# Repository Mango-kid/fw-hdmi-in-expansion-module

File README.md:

# Description
An HDMI input expansion module for the FW laptop. It utalizes the MS213x. As far as I can tell this is the highest preformance HDMI capture chip avalible that can fit in this package and not require serious thermal considerations. 
- USB3.0
- 100ms or better latency at 1080 in MJPEG mode (glass to glass, capture only will be less)

## Status
- hardware being prototyped and tested

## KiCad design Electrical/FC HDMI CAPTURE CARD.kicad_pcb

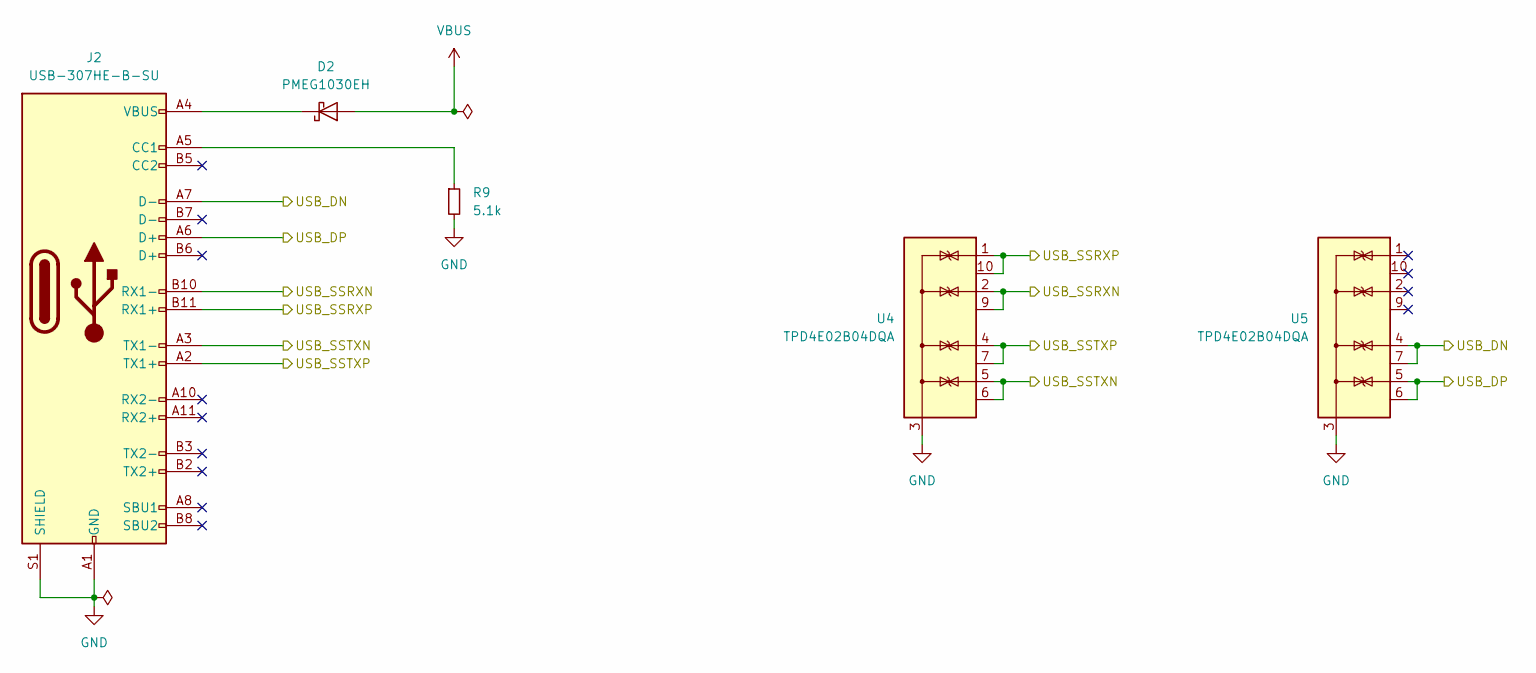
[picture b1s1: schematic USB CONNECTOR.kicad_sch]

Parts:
D2: PMEG1030EH; D_SOD-123F
J2: USB-307HE-B-SU; USB-TYPE-C-SMD_USB-307HE-B-SU
R9: 5.1k; R_0402_1005Metric
U4, U5: TPD4E02B04DQA; USON-10_2.5x1.0mm_P0.5mm

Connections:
/CAPTURE CONTROLLER/USB_DN: J2.A7 (D-), U5.4 (IO3), U5.7 (NC); also elsewhere on the board
/CAPTURE CONTROLLER/USB_DP: J2.A6 (D+), U5.5 (IO4), U5.6 (NC); also elsewhere on the board
/CAPTURE CONTROLLER/USB_SSRXN: J2.B10 (RX1-), U4.2 (IO2), U4.9 (NC); also elsewhere on the board
/CAPTURE CONTROLLER/USB_SSRXP: J2.B11 (RX1+), U4.1 (IO1), U4.10 (NC); also elsewhere on the board
/CAPTURE CONTROLLER/USB_SSTXN: J2.A3 (TX1-), U4.5 (IO4), U4.6 (NC); also elsewhere on the board
/CAPTURE CONTROLLER/USB_SSTXP: J2.A2 (TX1+), U4.4 (IO3), U4.7 (NC); also elsewhere on the board
GND: J2.A1 (GND), J2.A12 (GND), J2.B1 (GND), J2.B12 (GND), J2.S1 (SHIELD), R9.2, U4.3 (G), U4.8 (G), U5.3 (G), U5.8 (G); also elsewhere on the board
unnamed: D2.1 (K), J2.A4 (VBUS), J2.A9 (VBUS), J2.B4 (VBUS), J2.B9 (VBUS)
unnamed: J2.A5 (CC1), R9.1
VBUS: D2.2 (A); also elsewhere on the board

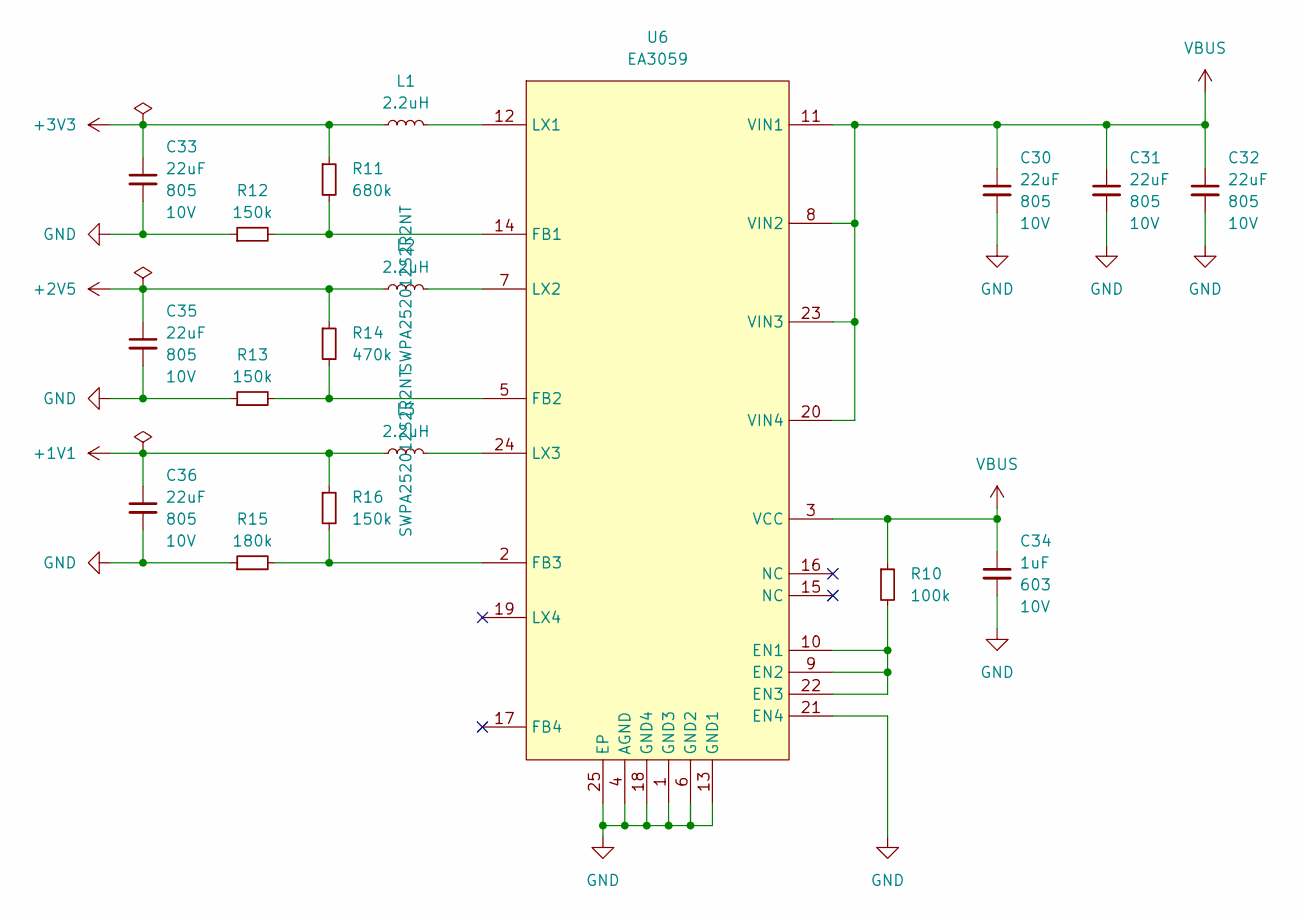
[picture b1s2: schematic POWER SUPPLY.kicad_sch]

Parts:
C30, C31, C32, C33, C35, C36: 22uF; C_0805_2012Metric; VOLTAGE 10V
C34: 1uF; C_0603_1608Metric; VOLTAGE 10V
L1, L2, L3: 2.2uH; L_1008_2520Metric; MPN SWPA252012S2R2NT
R10: 100k; R_0402_1005Metric
R11: 680k; R_0402_1005Metric
R12, R13, R16: 150k; R_0402_1005Metric
R14: 470k; R_0402_1005Metric
R15: 180k; R_0402_1005Metric
U6: EA3059; QFN-24-1EP_4x4mm_P0.5mm_EP2.5x2.5mm

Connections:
+1V1: C36.1, L3.1, R16.1; also elsewhere on the board
+2V5: C35.1, L2.1, R14.1; also elsewhere on the board
+3V3: C33.1, L1.1, R11.1; also elsewhere on the board
GND: C30.2, C31.2, C32.2, C33.2, C34.2, C35.2, C36.2, R12.1, R13.1, R15.1, U6.1 (GND3), U6.4 (AGND), U6.6 (GND2), U6.13 (GND1), U6.18 (GND4), U6.21 (EN4), U6.25 (EP); also elsewhere on the board
unnamed: R10.2, U6.9 (EN2), U6.10 (EN1), U6.22 (EN3)
unnamed: R11.2, R12.2, U6.14 (FB1)
unnamed: R13.2, R14.2, U6.5 (FB2)
unnamed: R15.2, R16.2, U6.2 (FB3)
unnamed: L1.2, U6.12 (LX1)
unnamed: L2.2, U6.7 (LX2)
unnamed: L3.2, U6.24 (LX3)
VBUS: C30.1, C31.1, C32.1, C34.1, R10.1, U6.3 (VCC), U6.8 (VIN2), U6.11 (VIN1), U6.20 (VIN4), U6.23 (VIN3); also elsewhere on the board

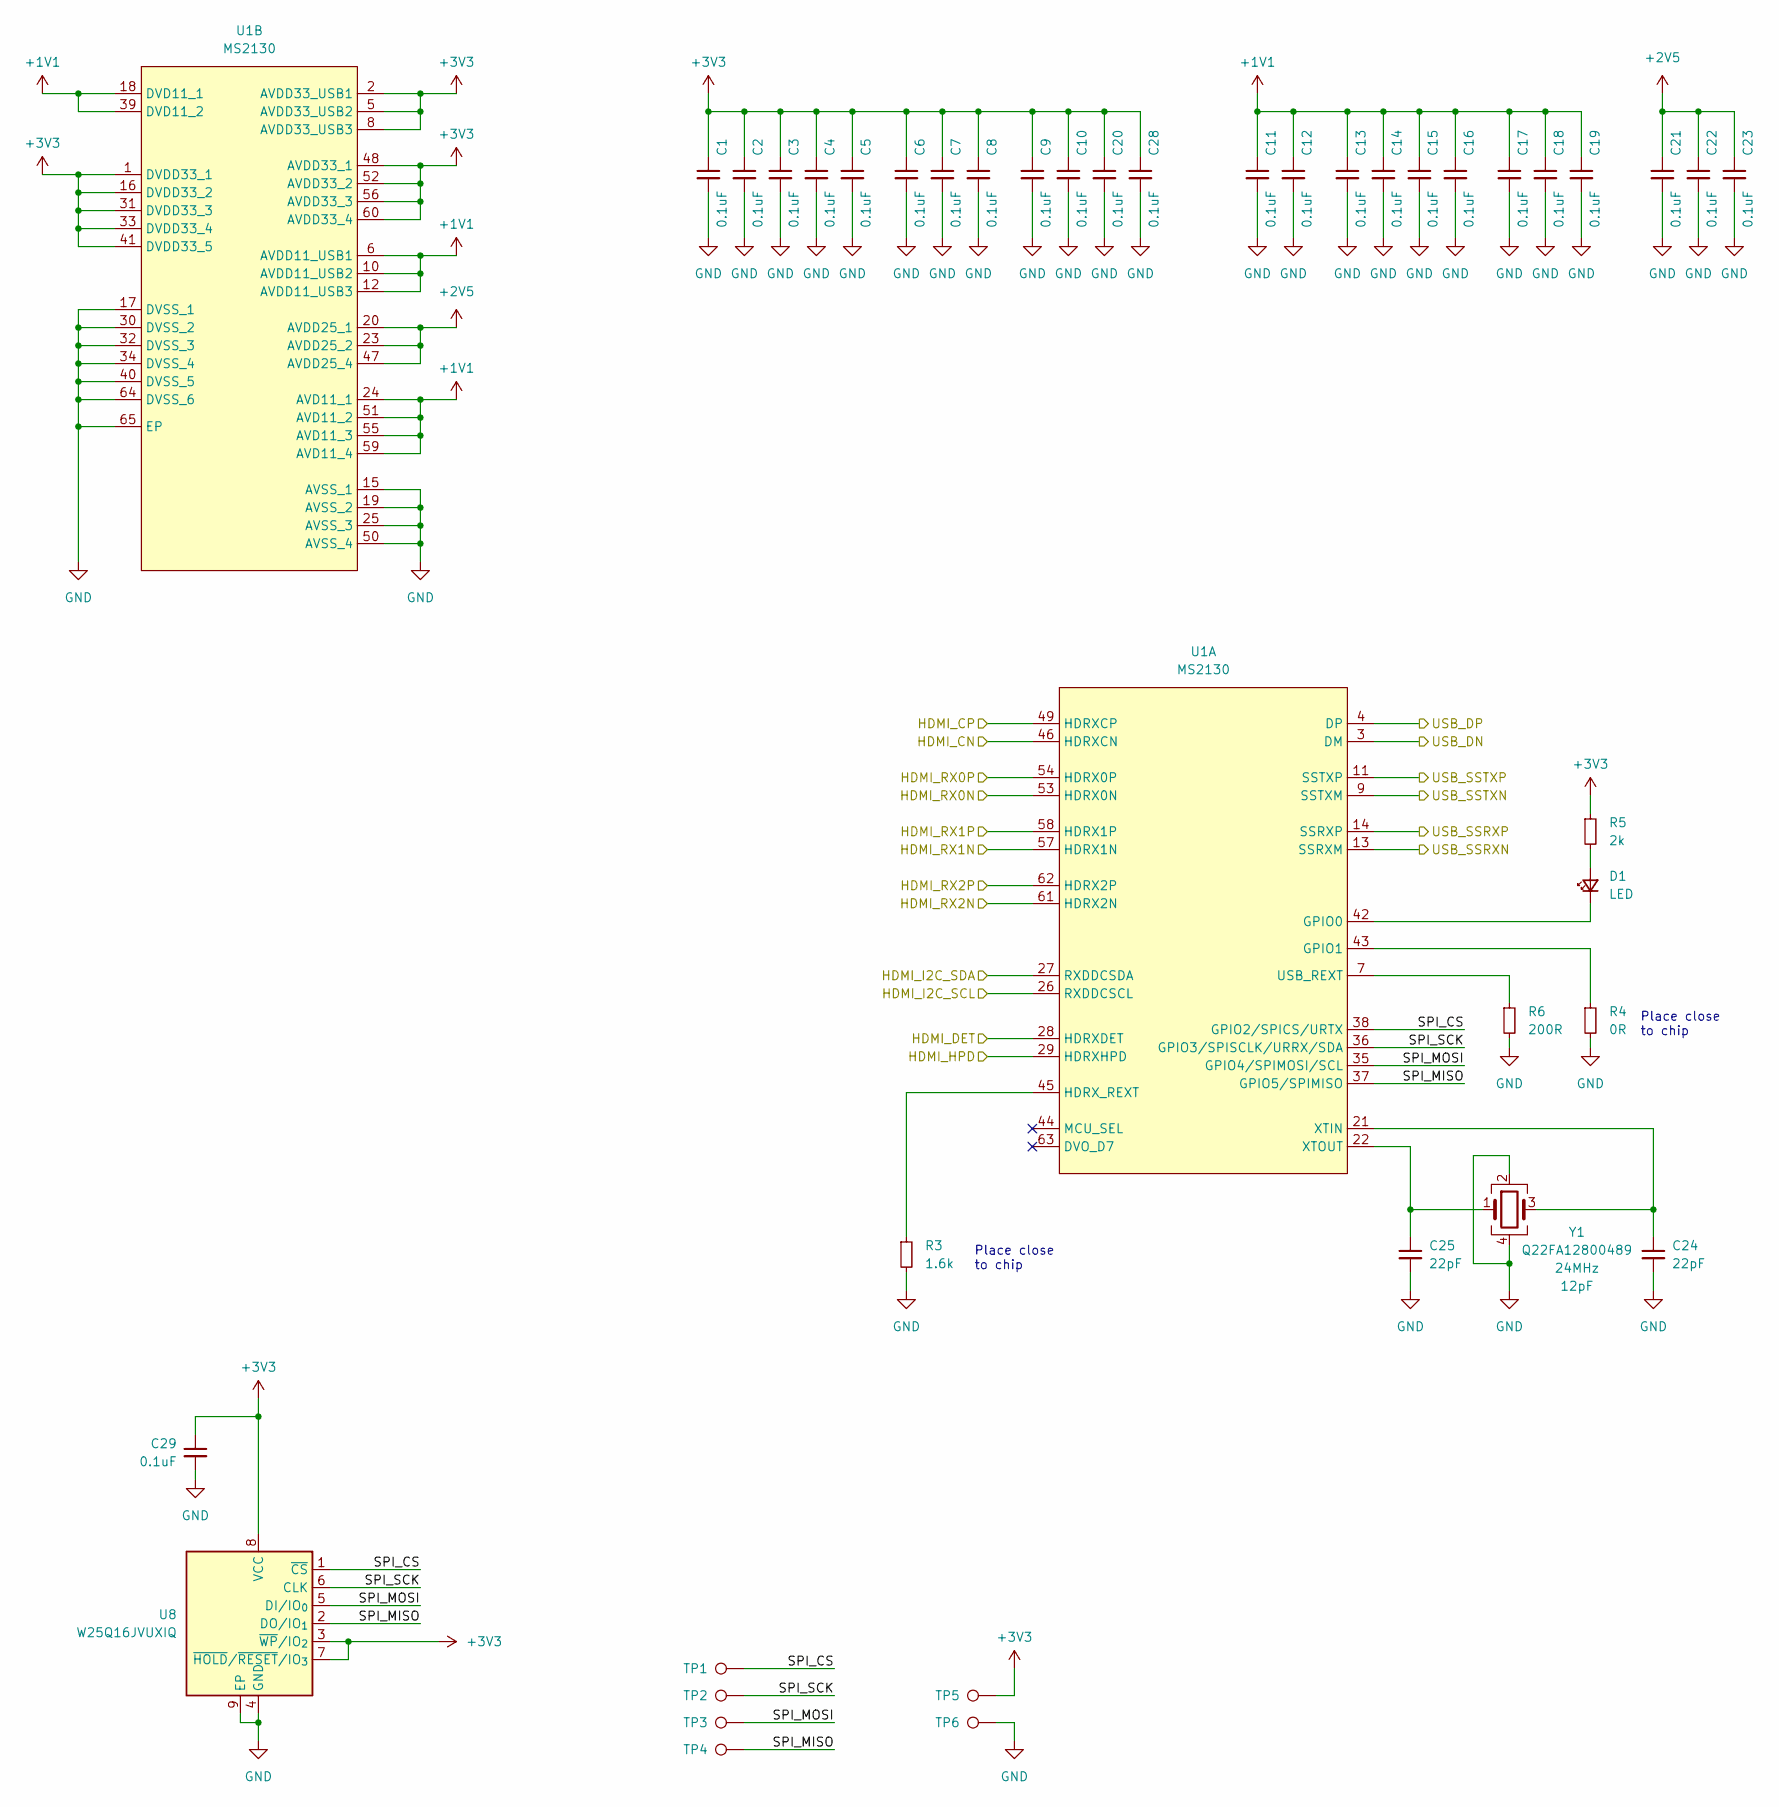
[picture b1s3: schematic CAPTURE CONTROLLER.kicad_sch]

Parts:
C1, C2, C3, C4, C5, C6, C7, C8, C9, C10, C11, C12, C13, C14, C15, C16, C17, C18, C19, C20, C21, C22, C23, C28, C29: 0.1uF; C_0402_1005Metric
C24, C25: 22pF; C_0402_1005Metric
D1: LED; LED_0402_1005Metric
R3: 1.6k; R_0402_1005Metric
R4: 0R; R_0402_1005Metric
R5: 2k; R_0402_1005Metric
R6: 200R; R_0402_1005Metric
TP1, TP2, TP3, TP4, TP5, TP6: TestPoint; TestPoint_Pad
U1: MS2130; QFN-64-1EP_9x9mm_P0.5mm_EP5.7x5.7mm
U8: W25Q16JVUXIQ; USON-8_L3.0-W2.0-P0.50-BL-EP
Y1: Q22FA12800489; Crystal_SMD_2016-4Pin_2.0x1.6mm

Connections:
+1V1: C11.1, C12.1, C13.1, C14.1, C15.1, C16.1, C17.1, C18.1, C19.1, U1.6 (AVDD11_USB1), U1.10 (AVDD11_USB2), U1.12 (AVDD11_USB3), U1.18 (DVD11_1), U1.24 (AVD11_1), U1.39 (DVD11_2), U1.51 (AVD11_2), U1.55 (AVD11_3), U1.59 (AVD11_4); also elsewhere on the board
+2V5: C21.1, C22.1, C23.1, U1.20 (AVDD25_1), U1.23 (AVDD25_2), U1.47 (AVDD25_4); also elsewhere on the board
+3V3: C1.1, C2.1, C3.1, C4.1, C5.1, C6.1, C7.1, C8.1, C9.1, C10.1, C20.1, C28.1, C29.1, R5.1, TP5.1, U1.1 (DVDD33_1), U1.2 (AVDD33_USB1), U1.5 (AVDD33_USB2), U1.8 (AVDD33_USB3), U1.16 (DVDD33_2), U1.31 (DVDD33_3), U1.33 (DVDD33_4), U1.41 (DVDD33_5), U1.48 (AVDD33_1), U1.52 (AVDD33_2), U1.56 (AVDD33_3), U1.60 (AVDD33_4), U8.3 (~WP/IO_{2}), U8.7 (~HOLD/~RESET/IO_{3}), U8.8 (VCC); also elsewhere on the board
/CAPTURE CONTROLLER/HDMI_CN: U1.46 (HDRXCN); also elsewhere on the board
/CAPTURE CONTROLLER/HDMI_CP: U1.49 (HDRXCP); also elsewhere on the board
/CAPTURE CONTROLLER/HDMI_DET: U1.28 (HDRXDET); also elsewhere on the board
/CAPTURE CONTROLLER/HDMI_HPD: U1.29 (HDRXHPD); also elsewhere on the board
/CAPTURE CONTROLLER/HDMI_I2C_SCL: U1.26 (RXDDCSCL); also elsewhere on the board
/CAPTURE CONTROLLER/HDMI_I2C_SDA: U1.27 (RXDDCSDA); also elsewhere on the board
/CAPTURE CONTROLLER/HDMI_RX0N: U1.53 (HDRX0N); also elsewhere on the board
/CAPTURE CONTROLLER/HDMI_RX0P: U1.54 (HDRX0P); also elsewhere on the board
/CAPTURE CONTROLLER/HDMI_RX1N: U1.57 (HDRX1N); also elsewhere on the board
/CAPTURE CONTROLLER/HDMI_RX1P: U1.58 (HDRX1P); also elsewhere on the board
/CAPTURE CONTROLLER/HDMI_RX2N: U1.61 (HDRX2N); also elsewhere on the board
/CAPTURE CONTROLLER/HDMI_RX2P: U1.62 (HDRX2P); also elsewhere on the board
/CAPTURE CONTROLLER/SPI_CS: TP1.1, U1.38 (GPIO2/SPICS/URTX), U8.1 (~CS)
/CAPTURE CONTROLLER/SPI_MISO: TP4.1, U1.37 (GPIO5/SPIMISO), U8.2 (DO/IO_{1})
/CAPTURE CONTROLLER/SPI_MOSI: TP3.1, U1.35 (GPIO4/SPIMOSI/SCL), U8.5 (DI/IO_{0})
/CAPTURE CONTROLLER/SPI_SCK: TP2.1, U1.36 (GPIO3/SPISCLK/URRX/SDA), U8.6 (CLK)
/CAPTURE CONTROLLER/USB_DN: U1.3 (DM); also elsewhere on the board
/CAPTURE CONTROLLER/USB_DP: U1.4 (DP); also elsewhere on the board
/CAPTURE CONTROLLER/USB_SSRXN: U1.13 (SSRXM); also elsewhere on the board
/CAPTURE CONTROLLER/USB_SSRXP: U1.14 (SSRXP); also elsewhere on the board
/CAPTURE CONTROLLER/USB_SSTXN: U1.9 (SSTXM); also elsewhere on the board
/CAPTURE CONTROLLER/USB_SSTXP: U1.11 (SSTXP); also elsewhere on the board
GND: C1.2, C2.2, C3.2, C4.2, C5.2, C6.2, C7.2, C8.2, C9.2, C10.2, C11.2, C12.2, C13.2, C14.2, C15.2, C16.2, C17.2, C18.2, C19.2, C20.2, C21.2, C22.2, C23.2, C24.2, C25.2, C28.2, C29.2, R3.2, R4.2, R6.2, TP6.1, U1.15 (AVSS_1), U1.17 (DVSS_1), U1.19 (AVSS_2), U1.25 (AVSS_3), U1.30 (DVSS_2), U1.32 (DVSS_3), U1.34 (DVSS_4), U1.40 (DVSS_5), U1.50 (AVSS_4), U1.64 (DVSS_6), U1.65 (EP), U8.4 (GND), U8.9 (EP), Y1.2, Y1.4; also elsewhere on the board
unnamed: D1.2 (A), R5.2
unnamed: D1.1 (K), U1.42 (GPIO0)
unnamed: R4.1, U1.43 (GPIO1)
unnamed: R3.1, U1.45 (HDRX_REXT)
unnamed: R6.1, U1.7 (USB_REXT)
unnamed: C24.1, U1.21 (XTIN), Y1.3
unnamed: C25.1, U1.22 (XTOUT), Y1.1

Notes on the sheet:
Place close to chip

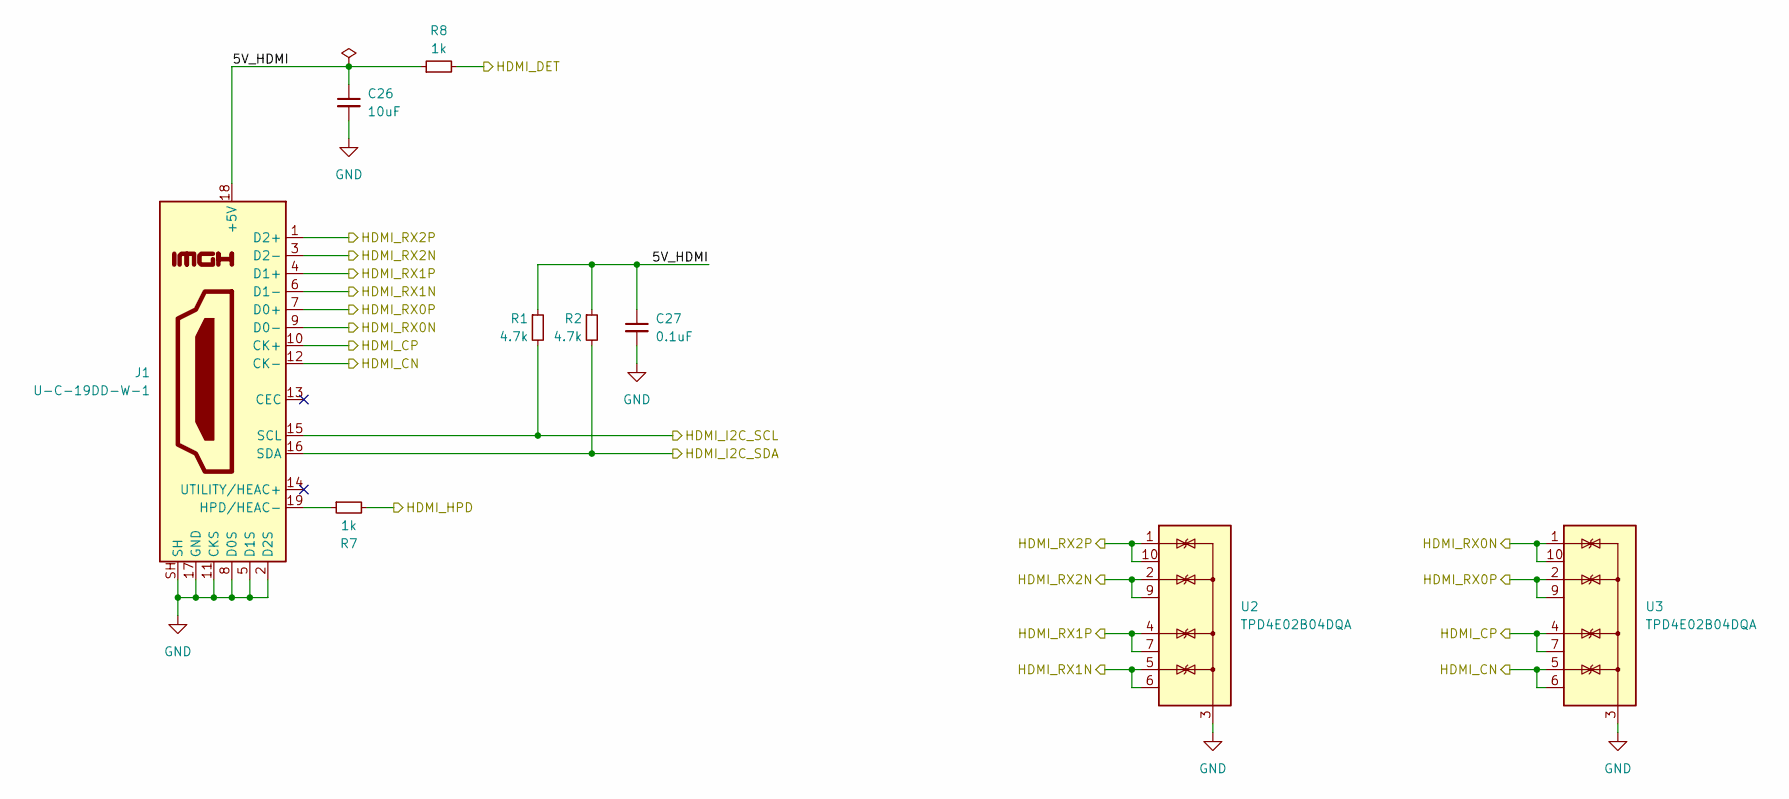
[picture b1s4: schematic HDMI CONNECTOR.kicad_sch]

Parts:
C26: 10uF; C_0603_1608Metric
C27: 0.1uF; C_0402_1005Metric
J1: U-C-19DD-W-1; SAMESKY_HD06-19-RVS-MSMT-TR
R1, R2: 4.7k; R_0402_1005Metric
R7, R8: 1k; R_0402_1005Metric
U2, U3: TPD4E02B04DQA; USON-10_2.5x1.0mm_P0.5mm

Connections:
/CAPTURE CONTROLLER/HDMI_CN: J1.12 (CK-), U3.5 (IO4), U3.6 (NC); also elsewhere on the board
/CAPTURE CONTROLLER/HDMI_CP: J1.10 (CK+), U3.4 (IO3), U3.7 (NC); also elsewhere on the board
/CAPTURE CONTROLLER/HDMI_DET: R8.2; also elsewhere on the board
/CAPTURE CONTROLLER/HDMI_HPD: R7.2; also elsewhere on the board
/CAPTURE CONTROLLER/HDMI_I2C_SCL: J1.15 (SCL), R1.2; also elsewhere on the board
/CAPTURE CONTROLLER/HDMI_I2C_SDA: J1.16 (SDA), R2.2; also elsewhere on the board
/CAPTURE CONTROLLER/HDMI_RX0N: J1.9 (D0-), U3.1 (IO1), U3.10 (NC); also elsewhere on the board
/CAPTURE CONTROLLER/HDMI_RX0P: J1.7 (D0+), U3.2 (IO2), U3.9 (NC); also elsewhere on the board
/CAPTURE CONTROLLER/HDMI_RX1N: J1.6 (D1-), U2.5 (IO4), U2.6 (NC); also elsewhere on the board
/CAPTURE CONTROLLER/HDMI_RX1P: J1.4 (D1+), U2.4 (IO3), U2.7 (NC); also elsewhere on the board
/CAPTURE CONTROLLER/HDMI_RX2N: J1.3 (D2-), U2.2 (IO2), U2.9 (NC); also elsewhere on the board
/CAPTURE CONTROLLER/HDMI_RX2P: J1.1 (D2+), U2.1 (IO1), U2.10 (NC); also elsewhere on the board
/HDMI CONNECTOR/5V_HDMI: C26.1, C27.1, J1.18 (+5V), R1.1, R2.1, R8.1
GND: C26.2, C27.2, J1.2 (D2S), J1.5 (D1S), J1.8 (D0S), J1.11 (CKS), J1.17 (GND), J1.SH, U2.3 (G), U2.8 (G), U3.3 (G), U3.8 (G); also elsewhere on the board
unnamed: J1.19 (HPD/HEAC-), R7.1

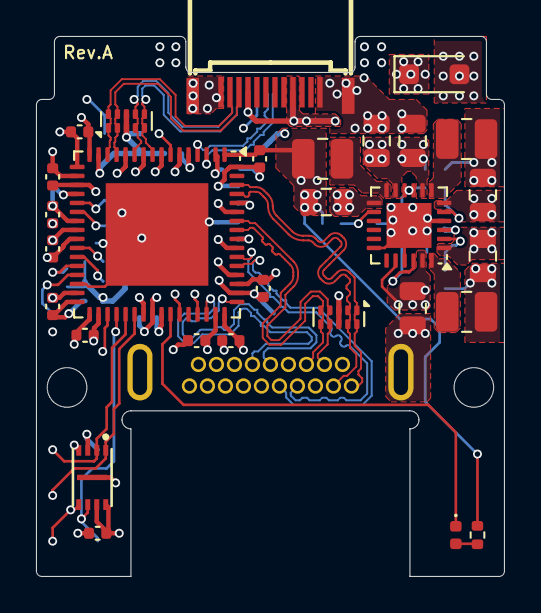
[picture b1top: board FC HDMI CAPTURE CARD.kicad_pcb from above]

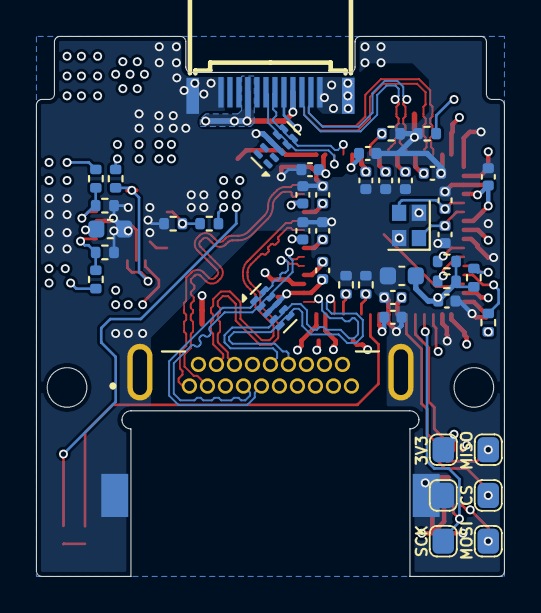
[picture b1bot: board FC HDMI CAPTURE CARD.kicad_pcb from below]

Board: 6 copper layers, 26.0 x 30.0 mm, 75 parts (44 on the bottom side), 45 nets.

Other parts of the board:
H1, H2: MountingHole; MountingHole_2.2mm_M2

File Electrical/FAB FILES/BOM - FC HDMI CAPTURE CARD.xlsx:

Designator | Qnty | Comment | Footprint | LCSC Part # | Externally Sourced | REMARK
C1,C2,C3,C4,C5,C6,C7,C8,C9,C10,C11,C12,C13,C14,C15,C16,C17,C18,C19,C20,C21,C22,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 | 26 | 0.1uF | 402
C24,C25 | 2 | 22pF | 402
C26 | 1 | 10uF | 603
C30,C31,C32,C33,C35,C36 | 6 | 22uF | 805 | C45783
C34 | 1 | 1uF | 603
D1 | 1 | LED | 402
D2 | 1 | PMEG1030EH | SOD-123F | C552800
J1 | 1 | HD06-19-RVS-MSMT-TR | HD06-19-RVS-MSMT-TR |  | HD06-19-RVS-MSMT-TR
J2 | 1 | USB-307HE-B-SU | SMD | C309351
L1,L2,L3 | 3 | 2.2uH | 1008 | C36400
R1,R2 | 2 | 4.7k | 402
R3 | 1 | 1.6k | 402
R4 | 1 | 0R | 402
R5 | 1 | 2k | 402
R6 | 1 | 200R | 402
R7,R8 | 2 | 1k | 402
R9 | 1 | 5.1k | 402
R10 | 1 | 100k | 402
R11 | 1 | 680k | 402
R12,R13,R16 | 3 | 150k | 402
R14 | 1 | 470k | 402
R15 | 1 | 180k | 402
U1 | 1 | MS2130 | QFN-64-EP(9x9) | C5905137
U2,U3,U4,U5 | 4 | TPD4E02B04DQA | USON-10(1x2.5) | C106794
U6 | 1 | EA3059 | QFN-24-EP(4x4) | C111586
U8 | 1 | W25Q16JVUXIQ | USON-8-EP(2x3) | C2843335
Y1 | 1 | Q22FA12800489 | Crystal:Crystal_SMD_2016-4Pin_2.0x1.6mm | C255882

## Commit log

2025-04-14 first prototype hardware
2025-04-14 added readme
